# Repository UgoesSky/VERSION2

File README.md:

# What we are doing here?
We develop an balloon for the Stratosphere. We are a small group of students from a bording school in southern Germany, near Ulm. In 2014 we had the idea to develop and launch an balloon into the Stratosphere. Our first balloon launched on 20 March 2015 during the partial solar eclipse in Europe. At almost 22 km, our balloon, filled with helium, burst. The capsule landed save, hanging on a parachute.

Now we are developing our second balloon. We target this launch in Summer 2016.
# VERSION2
Die Daten für V2 des Ballonprojekts 'UgoesSky'.

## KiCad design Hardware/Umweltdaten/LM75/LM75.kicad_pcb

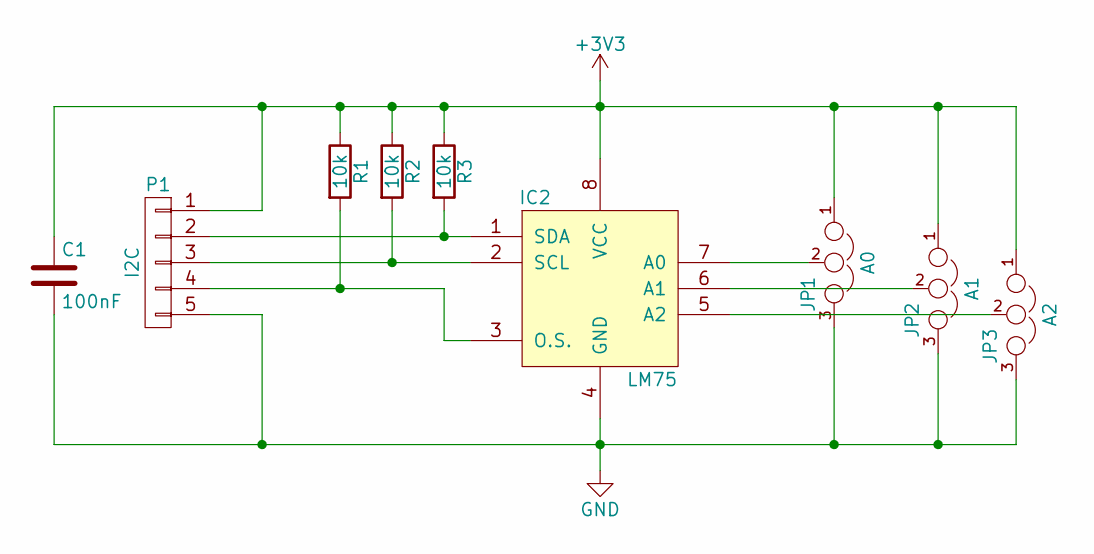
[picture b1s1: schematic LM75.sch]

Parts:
C1: 100nF; C_0805_HandSoldering
IC2: LM75; SOIC-8-N
JP1: A0; SJ_2
JP2: A1; SJ_2
JP3: A2; SJ_2
P1: I2C; SMD_05-4mm
R1, R2, R3: 10k; R_0805_HandSoldering

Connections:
+3V3: C1.1, IC2.8 (VCC), JP1.1, JP2.1, JP3.1, P1.1, R1.1, R2.1, R3.1
GND: C1.2, IC2.4 (GND), JP1.3, JP2.3, JP3.3, P1.5
unnamed: IC2.1 (SDA), P1.2, R3.2
unnamed: IC2.2 (SCL), P1.3, R2.2
unnamed: IC2.3 (O.S.), P1.4, R1.2
unnamed: IC2.5 (A2), JP3.2
unnamed: IC2.6 (A1), JP2.2
unnamed: IC2.7 (A0), JP1.2

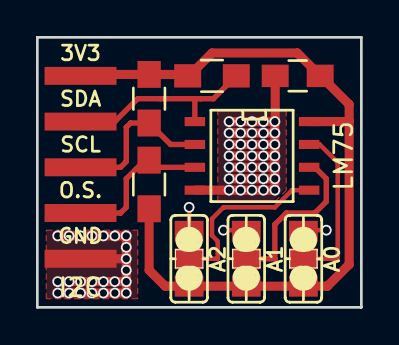
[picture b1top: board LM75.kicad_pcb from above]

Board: 2 copper layers, 18.0 x 15.0 mm, 9 parts (0 on the bottom side), 8 nets.

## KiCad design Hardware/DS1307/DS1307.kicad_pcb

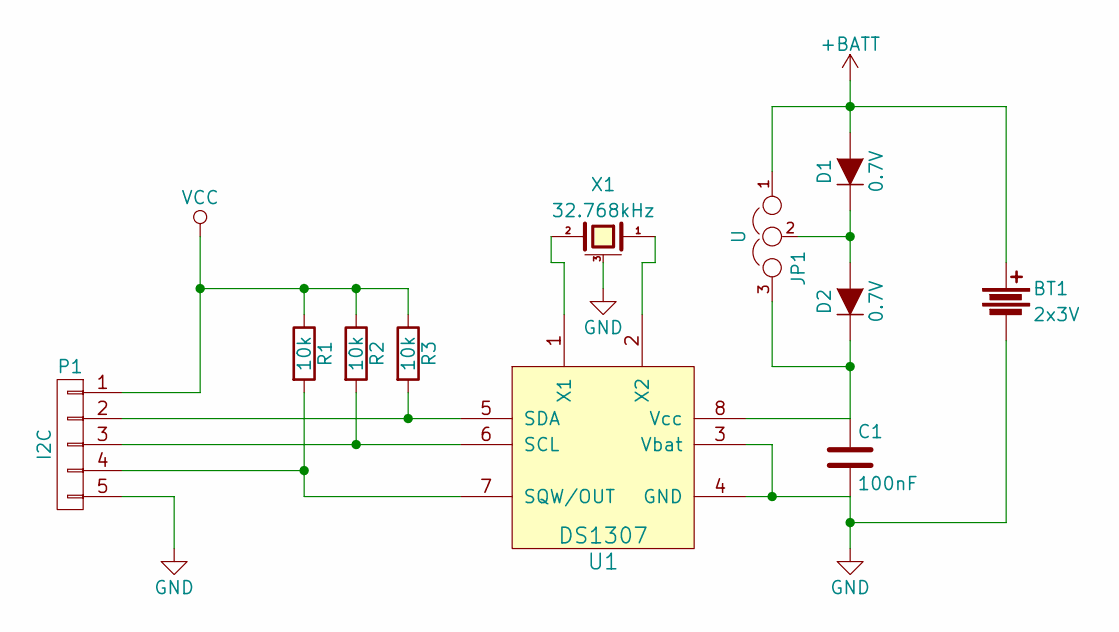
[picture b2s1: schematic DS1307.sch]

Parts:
BT1: 2x3V; KZH-20
C1: 100nF; C_0805_HandSoldering
D1, D2: 0.7V; R_1206_HandSoldering
JP1: U; SJ_2
P1: I2C; SMD_05-4mm
R1, R2, R3: 10k; R_0805_HandSoldering
U1: DS1307; SOIC-8_3.9x4.9mm_Pitch1.27mm
X1: 32.768kHz; MS1V-T1K

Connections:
+BATT: BT1.1, D1.2 (A), JP1.1
GND: BT1.2, C1.2, P1.5, U1.3 (Vbat), U1.4 (GND), X1.3 (case)
unnamed: C1.1, D2.1 (K), JP1.3, U1.8 (Vcc)
unnamed: D1.1 (K), D2.2 (A), JP1.2
unnamed: P1.2, R3.2, U1.5 (SDA)
unnamed: P1.3, R2.2, U1.6 (SCL)
unnamed: P1.4, R1.2, U1.7 (SQW/OUT)
unnamed: U1.1 (X1), X1.2
unnamed: U1.2 (X2), X1.1
VCC: P1.1, R1.1, R2.1, R3.1

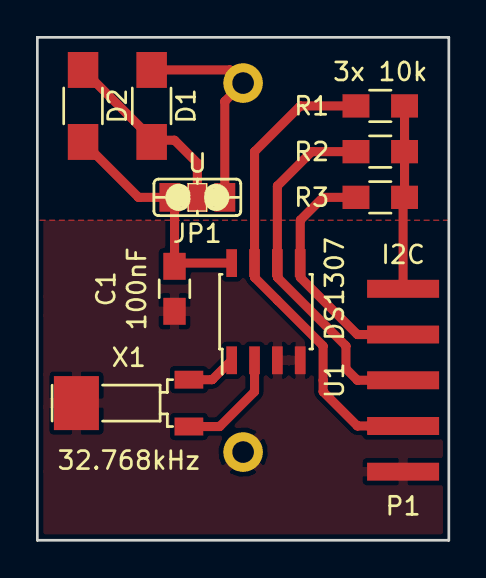
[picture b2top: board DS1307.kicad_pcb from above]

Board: 2 copper layers, 22.9 x 27.9 mm, 11 parts (1 on the bottom side), 10 nets.

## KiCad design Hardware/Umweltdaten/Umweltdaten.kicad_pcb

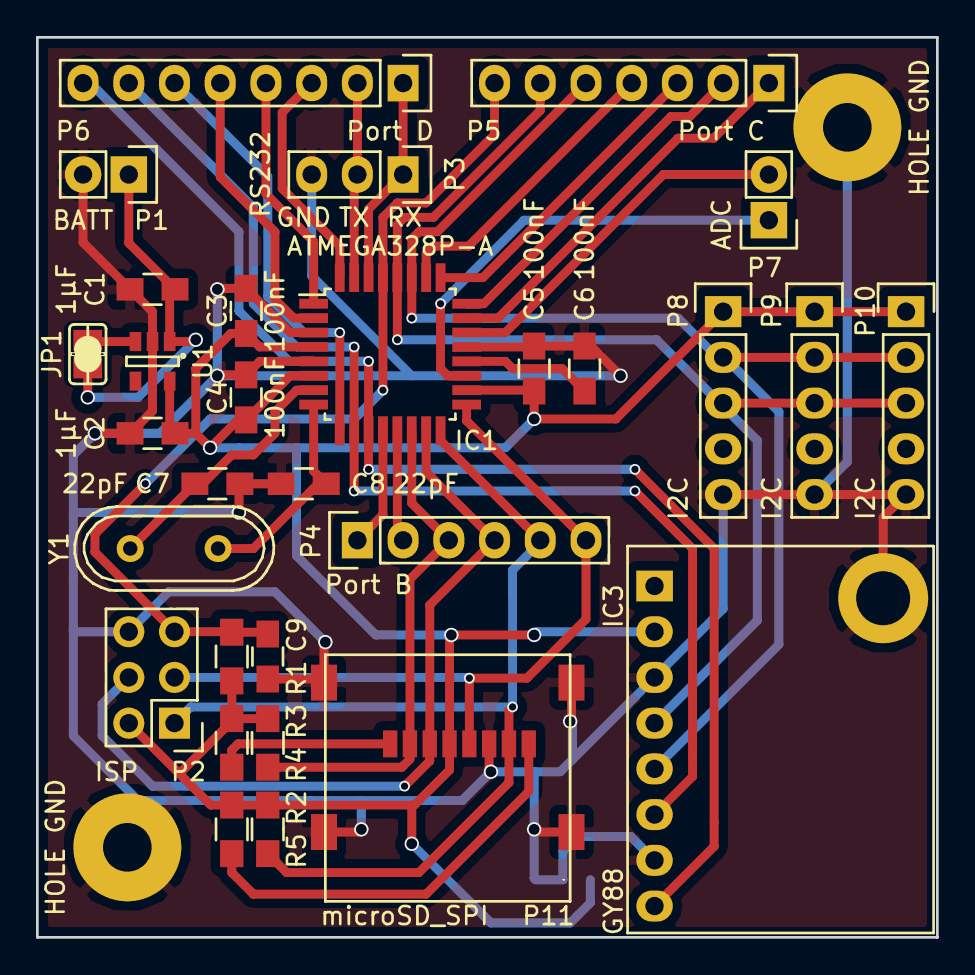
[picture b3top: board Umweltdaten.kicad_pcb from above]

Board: 2 copper layers, 50.0 x 50.0 mm, 33 parts (1 on the bottom side), 31 nets.

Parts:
C1, C2: 1µF; C_0805_HandSoldering
C3, C4, C5, C6, C9: 100nF; C_0805_HandSoldering
C7, C8: 22pF; C_0805_HandSoldering
HOLE GND: MountingHole_2-7mm
HOLE GND#2: MountingHole_2-7mm
IC1: ATMEGA328P-A; TQFP-32_7x7mm_Pitch0.8mm
IC3: GY88
JP1: Ureg EN; SJ
JP2: G_AD0; SJ_2
P1: BATT; Pin_Header_Straight_1x02
P2: ISP; Pin_Header_Straight_2x03
P3: RS232; Pin_Header_Straight_1x03
P4: Port B; Pin_Header_Straight_1x06
P5: Port C; Pin_Header_Straight_1x07
P6: Port D; Pin_Header_Straight_1x08
P7: ADC; Pin_Header_Straight_1x02
P8, P9, P10: I2C; Pin_Header_Straight_1x05
P11: microSD_SPI; microSD
R1, R2, R3, R4, R5: 10k; R_0805_HandSoldering
U1: TLV70233DBV; SOT-23-5
Y1: Crystal 16Mhz; Crystal_HC49-U_Vertical

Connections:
+3V3: C2.1, C3.1, C4.1, C5.1, IC1.4, IC1.6, IC1.18, IC3.2, JP2.1, P2.2, P8.1, P9.1, P10.1, P11.4, R1.1, R2.1, R3.1, R4.1, R5.1, U1.5
+BATT: C1.1, JP1.1, JP1.2, P1.1, U1.1, U1.3
ADC6: IC1.19, P7.1
ADC7: IC1.22, P7.2
GND: C1.2, C2.2, C3.2, C4.2, C5.2, C6.2, C7.2, C8.2, C9.2, HOLE GND.1, HOLE GND#2.1, IC1.3, IC1.5, IC1.21, IC3.3, IC3.7, JP2.2, JP2.3, P1.2, P2.6, P3.3, P8.5, P9.5, P10.5, P11.6, P11.9, P11.10, P11.11, P11.12, U1.2
MISO: IC1.16, P2.1, P4.5, P11.7, R2.2
unnamed: C6.1, IC1.20
unnamed: P11.1, R4.2
unnamed: P11.8, R5.2
PB0: IC1.12, P4.1
PB1: IC1.13, P4.2
PB2: IC1.14, P4.3, P11.2, R3.2
PB3: IC1.15, P2.4, P4.4, P11.3
PB6: C7.1, IC1.7, Y1.1
PC0: IC1.23, P5.1
PC1: IC1.24, P5.2
PC2: IC1.25, P5.3
PC3: IC1.26, P5.4
PC6: C9.1, IC1.29, P2.5, P5.7, R1.2
PD0: IC1.30, P3.1, P6.1
PD2: IC1.32, P6.3
PD3: IC1.1, P6.4
PD4: IC1.2, P6.5
PD5: IC1.9, P6.6
PD6: IC1.10, IC3.6, P6.7
PD7: IC1.11, IC3.8, P6.8
SCK: IC1.17, P2.3, P4.6, P11.5
SCL: IC1.28, IC3.4, P5.6, P8.3, P9.3, P10.3
SDA: IC1.27, IC3.5, P5.5, P8.2, P9.2, P10.2
TX: IC1.31, P3.2, P6.2
XTAL2: C8.1, IC1.8, Y1.2

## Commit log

2015-06-05 Dann mal los
    Vorarbeiten von Version 1. Frohes Schaffen!
2015-06-05 Update sstv.sh
    Wir haben was zu tun!
2015-06-05 altes hinzugefuegt
2015-06-05 Git Anleitung für doof
2015-06-06 Kopie von Rufzeichen und Testbild
2015-06-06 Fehler behoben
2015-06-06 Readme
2015-06-21 GY88 3.3V Umbau Schaltplan
2015-06-21 GY88 Foto
2015-06-22 sstv logging
2015-06-28 GY88 3.3V Umbau Layout
2015-06-28 Foto entfernt
2015-08-10 cleaning the code
2015-08-18 add Umweltdaten schema
2015-08-19 add some things
2015-08-19 add some things and fix ERC errors
2015-08-19 add PDF schema
2015-08-20 add footprint assignment
2015-08-20 routing PCB
2015-08-21 finish schema and PCB
2015-08-22 add silkscreen and fix DRC errors
2015-08-22 add gerber files
2015-08-22 add pictures
2015-09-20 add logos and bom
2015-09-20 add LM/TMP75 PCB
2015-09-20 update schema
2015-09-22 Log erweitert
2015-10-17 Platine V2-final
2015-11-06 files changed while ordering the pcb
2015-11-06 TMP75 arduino sketch added
2015-11-06 BMP085 arduino sketch added
2015-11-06 Revert "BMP085 arduino sketch added"
    This reverts commit c30323349d64004dd2e94f92d630d01dd3fd3dc9.
2015-11-06 Revert "Revert "BMP085 arduino sketch added""
    This reverts commit 1e19f4affd4d484d9b8227db6644ecbaaca4d60d.
2015-11-06 make some wrong things back
2015-11-06 BMP085 and TMP75 arduino sketch added
2015-12-29 Programmcode kommentiert
2015-12-29 Datumsfeher
2015-12-30 Menge skripte into Software
2016-04-12 update TMP75 long sketch
2016-04-12 add issues file
2016-04-14 put TMP75 in a function
2016-04-19 Update Umweltdaten
2016-04-24 change variables from int to float to enable higher temperature resulution
2016-04-24 Revert "Update Umweltdaten"
    This reverts commit 07671d206f2da155dbf86959c01b7aa278c26477.
2016-05-14 put all programms together into SD
2016-05-15 LM/TMP75 layout
2016-05-16 finished LM/TMP75 PCB
2016-05-29 edited issues
2016-05-29 RTC DS1307 schematic and layout
2016-06-04 work on layout
2016-06-04 finished DS1307 and renamed it
2016-06-05 create Gerber files
2016-06-08 sketch for DS1307
2016-06-08 changed some things
2016-06-08 put DS1307 and time in SD
2016-06-21 changed TMP75 address and updated the configuration things
2016-06-26 Update issues
2016-06-26 put into git issue
2016-06-28 add battery voltage
2016-06-28 add DHT22
2016-06-30 fix issue with endless loop when BMP085 not available
2016-07-01 fix from commit b65cb30
2016-07-02 Preperation for impementation DHT22
    send Data from DHT22 via SSTV to ground
2016-07-02 Update sstv.
    some trouble
2016-07-13 RTC and DHT with RPi
2016-07-26 Umweltdaten Auswertung
